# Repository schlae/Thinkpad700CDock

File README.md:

# Thinkpad 700C Dock Slot Adapter
This set of boards allows you to connect Micro Channel expansion boards to an IBM Thinkpad 700, 700C, 720, or 720C. This is an experimental project based on a lot of my own reverse engineering work, so don't expect it to work perfectly.

The AMP Champ connector appears to be out of production, so this project uses two stacked circuit boards that are slightly thinner (1.2mm) than a normal PC board. The 1.2mm thickness allows the boards, after stacking, to plug right into the docking connector.

## Fabbing and Assembly

Be sure to specify 1.2mm thickness for all the boards!

There are three boards total. The first two are both boards that plug into the lower part of the docking connector. Pick one of them.

* 700CDockSlot - Oriented so a connected Micro Channel card bracket points toward the left edge of the LCD display as viewed from the front. This provides easy access to the component side of the Micro Channel card from behind the laptop.
* 700CDockSlotFlipped - Oriented so a connected Micro Channel expansion card bracket sits at the right edge of the LCD display as viewed from the front. Turning the laptop around, you will see the solder side of an attached Micro Channel expansion card.

The third board plugs into the upper part of the docking connector.

* 700CDockSlotUpper - Provides wiring for IRQ10, IRQ11, IRQ12, IRQ14, and IRQ15.

If you know you won't need those IRQ lines, then you don't need this board.

Once you've soldered up both boards, attach them together using wires connecting the two boards together through J2. Use 1.6mm thick washers or 3D printed spacers in between the boards.

## Configuration

Jumper block J8 lets you select the source of the main 5V rail. Typically you will want to use the 5V position, which is an always-on 5V source. The 5VD position uses the 5V source that shuts off when the laptop is in standby mode. This isn't desirable since the laptop BIOS does not reinitialize and reenable any cards plugged into the adapter.

Test points J9 and J10 are for providing an external source of +12V for cards that require a lot of current (like hard cards or whatever).

## Known Issues

Revision 1 of the design had a few design errors that were fixed in rev 2. In case you have an old revision board, you will need to make the following changes:

* CHRESET should be tied to pin 102 of the docking connector. 
* MADE24 has not been found on the docking connector yet. Most likely this is because the machine never has more than 16M of RAM and it does not support 32-bit cards.

To fix the CHRESET issue, remove U3 and R3. Cut the MADE24 trace at the Micro Channel slot connector (pin A2) and run a wire from pin 102 of the expansion edge connector to U3 pin 2. Connect a 10K resistor from the MADE24 pin of the MCA bus connector (pin A2) to a nearby +5C net (like pin A7).

Signal integrity isn't all that good, but these older 5V logic systems were not known for good signal integrity. The original IBM docking cartridge uses some buffer chips presumably for improving this on some signals, but I don't have access to one nor do I have access to high-resolution photos, so the mystery remains.

Certain types of cards will not work with this setup. Memory cards that use the matched memory extension won't physically fit, and wouldn't work anyway because the 700C doesn't bring out the necessary bus signals. I have not wired up the signals for the Auxiliary Video Extension, so cards supporting this won't work either.

The docking connector brings out a single CD\_SETUP# signal for slot 2, limiting this adapter to a single card slot. In theory it would be possible to support more than one slot; more research is necessary.

# Thinkpad 700C Docking Connector Information
Through a rather tedious manual process, I've been able to reverse engineer the docking connector for this laptop.

| Bottom row (wide end) | Row 2 | Row 3 | Top row (narrow end) |
|-----------------------|-------|-------|----------------------|
| 1: PWR\_SWITCH#         | 61: CD\_SETUP# (slot 2) | 121: +5V              | 181: +5V |
| 2: Unknown, to 39G8600  | 62: GND                 | 122: +10V             | 182: +5V |
| 3: GND                  | 63: AUDIO SUM           | 123: GND              | 183: +5V |
| 4: OSC (14.318MHz)      | 64: GND                 | 124: PS/2 mouse pin 2 | 184: PS/2 mouse pin 1 | 
| 5: GND                  | 65: A23                 | 125: PS/2 mouse pin 6 | 185: PS/2 mouse pin 5 |
| 6: A6                   | 66: A22                 | 126: GND              | 186: GND |
| 7: +5V                  | 67: A21                 | 127: n/c              | 187: GND |
| 8: A5                   | 68: A20                 | 128: n/c              | 188: GND |
| 9: +5V                  | 69: A19                 | 129: n/c              | 189: GND |
| 10: A4                  | 70: A18                 | 130: n/c              | 190: n/c |
| 11: GND                 | 71: A17                 | 131: n/c              | 191: GND |
| 12: A3                  | 72: A16                 | 132: n/c              | 192: GND |
| 13: 5V\_2               | 73: A15                 | 133: n/c              | 193: GND |
| 14: A2                  | 74: A14                 | 134: n/c              | 194: n/c |
| 15: 5V\_2               | 75: A13                 | 135: n/c              | 195: GND |
| 16: A1                  | 76: A12                 | 136: n/c              | 196: GND |
| 17: 5V\_2               | 77: A11                 | 137: n/c              | 197: n/c |
| 18: A0                  | 78: A10                 | 138: n/c              | 198: n/c |
| 19: GND                 | 79: A9                  | 139: n/c              | 199: GND |
| 20: ADL#                | 80: A8                  | 140: n/c              | 200: n/c |
| 21: GND                 | 81: A7                  | 141: n/c              | 201: GND |
| 22: S0 (WR#)            | 82: PREEMPT#            | 142: n/c              | 202: n/c |
| 23: 5V\_2               | 83: BURST#              | 143: n/c              | 203: GND |
| 24: S1 (RD#)            | 84: IRQ9#               | 144: n/c              | 204: n/c |
| 25: 5V\_2               | 85: IRQ3#               | 145: LED5 (floppy)    | 205: LED1 (speaker green) |
| 26: M/IO#               | 86: IRQ4#               | 146: LED6 (HDD)       | 206: LED4 (left arrow) |
| 27: GND                 | 87: IRQ5#               | 147: REFRESH (positive) | 207: GND |
| 28: CMD#                | 88: IRQ6#               | 148: ESYNC# (AVE)     | 208: VSYNC (AVE) |
| 29: GND                 | 89: IRQ7#               | 149: P7 (AVE)         | 209: HSYNC (AVE) |
| 30: ARB/GNT#            | 90: ARB0                | 150: P6 (AVE)         | 210: BLANK (AVE) |
| 31: n/c                 | 91: ARB1                | 151: P5 (AVE)         | 211: GND |
| 32: TC#                 | 92: ARB2                | 152: P4 (AVE)         | 212: DCLK (AVE) |
| 33: GND                 | 93: ARB3                | 153: P3 (AVE)         | 213: GND |
| 34: CHRDY#              | 94: CHCK#               | 154: P2 (AVE)         | 214: GND |
| 35: n/c                 | 95: CHRDYRTN#           | 155: P1 (AVE)         | 215: EDCLK# |
| 36: CD\_SFDBK#          | 96: DB0                 | 156: P0 (AVE)         | 216: EVIDEO# |
| 37: GND                 | 97: DB1                 | 157: Unknown, goes to 39G8600 | 217: GND |
| 38: DB3                 | 98: DB2                 | 158: IRQ11#           | 218: IRQ10# |
| 39: n/c                 | 99: DB4                 | 159: IRQ14#           | 219: IRQ12# |
| 40: DB6                 | 100: DB5                | 160: n/c (pulled up)  | 220: IRQ15# |
| 41: GND                 | 101: DB7                | 161: n/c (pulled up)  | 221: n/c (pulled up) |
| 42: CD\_DS16RTN#        | 102: CHRESET            | 162: n/c              | 222: GND |
| 43: n/c                 | 103: REFRESH#           | 163: Parallel port pin 9 | 223: Parallel port pin 13 |
| 44: +5V                 | 104: DB8                | 164: Parallel port pin 8 | 224: Parallel port pin 12 |
| 45: +5V                 | 105: DB9                | 165: Parallel port pin 7 | 225: Parallel port pin 11 |
| 46: DB11                | 106: DB10               | 166: Parallel port pin 6 | 226: GND |
| 47: GND                 | 107: DB12               | 167: Parallel port pin 5 | 227: Parallel port pin 10 |
| 48: GND                 | 108: DB13               | 168: Parallel port pin 4 | 228: Parallel port pin 17 |
| 49: n/c                 | 109: DB14               | 169: Parallel port pin 3 | 229: Parallel port pin 16 |
| 50: GND                 | 110: DB15               | 170: Parallel port pin 2 | 230: Parallel port pin 15 |
| 51: n/c                 | 111: CD\_DS16#          | 171: Parallel port pin 1 | 231: Parallel port pin 14 |
| 52: n/c                 | 112: SBHE#              | 172: STANDBY# (CN4 64) | 232: GND |
| 53: GND                 | 113: GND                | 173: Serial port pin 3   | 233: Serial port pin 2 |
| 54: +20V AC adapter     | 114: VGA port pin 3     | 174: Serial port pin 1   | 233: Serial port pin 4 |
| 55: +20V AC adapter     | 115: GND                | 175: Serial port pin 6   | 234: Serial port pin 8 |
| 56: +20V AC adapter     | 116: VGA port pin 2     | 176: Serial port pin 7   | 235: Serial port pin 9 |
| 57: +20V AC adapter     | 117: GND                | 177: VGA port pin 4      | 237: VGA port pin 15 |
| 58: +20V AC adapter     | 118: VGA port pin 1     | 178: VGA port pin 11     | 238: VGA port pin 12 |
| 59: +20V AC adapter     | 119: GND                | 179: +10V                | 239: GND |
| 60: +20V AC adapter     | 120: BACKLIGHT\_PWR# (CN4 29) | 180: GND | 240: GND |

Notes:

* 5V\_2 pins are always on. All remaining +5V pins turn off in standby mode.
* STANDBY# is at ~13V when the laptop is off, 5V during normal operation, and 0V during standby.

**Pin diagram (looking into the back of the laptop)**

The docking connector is in the AMP Champ .050 family, similar to the 5787886-1 but with 240 contacts instead of 200. I've had success connecting to the docking port using two stacked PCBs with 0.050" edge fingers. The PCBs need to be 1.2mm thick instead of the normal 1.6mm.

The docking port breaks out several ports on the laptop, for convenience:
* Parallel port
* Serial port
* PS/2 mouse port
* VGA port
* AC adapter

There also also all the signals required to implement a single Micro Channel expansion slot, including the Auxiliary Video Extension (AVE). This does not include the +12V and -12V rails. It also does not appear to break out the CHRESET signal.

Several pins implement functions specific to this laptop, including:
* PWR\_SWITCH#: Bring this line low to turn on the laptop. Connected in parallel with the physical power switch.
* LED1, LED4, LED5, LED6: Presumably a docking station could duplicate these LEDs (or perhaps control them?)
* SOFT\_POWEROFF#: Tied to the power board's connector pin 64.
* BACKLIGHT\_PWR#: Tied to the power board's connector pin 29.

# Thinkpad 700C Hard Disk Connector

The pinout for the hard disk drive is as follows:

| Pin | Function | Pin | Function |
|-----|----------|-----|----------|
| 1 | CHRESET#?  | 2 | CHRESET |
| 3 | SBHE#      | 4 | +5V |
| 5 | (key)      | 6 | S0 (WR#) |
| 7 | GND        | 8 | S1 (RD#) |
| 9 | CHRDY#     | 10 | GND |
| 11 | CMD# (buffered) | 12 | A3 |
| 13 | A2        | 14 | A1 |
| 15 | M/IO#     | 16 | A0 |
| 17 | ARB/GNT#  | 18 | TC# |
| 19 | IRQ14#    | 20 | DB13 |
| 21 | GND       | 22 | DB11 |
| 23 | DB10      | 24 | DB7 |
| 25 | ARB3      | 26 | ARB2 |
| 27 | GND       | 28 | ARB1 |
| 29 | ARB0      | 30 | BURST# |
| 31 | PREEMPT#  | 32 | DB6 |
| 33 | GND       | 34 | DB5 |
| 35 | DB2       | 36 | +5V |
| 37 | DB0       | 38 | DB15 |
| 39 | GND       | 40 | DB14 |
| 41 | DB12      | 42 | DB9 |
| 43 | GND       | 44 | DB8 |
| 45 | DB4       | 46 | +5V |
| 47 | DB3       | 48 | DB1 |
| 49 | GND       | 50 | CD\_DS16# (buffered) |
| 51 | CD\_SETUP# (slot 1) | 52 | ADDRESS\_SEL# |
| 53 | n/c | 54 | n/c |
| 55 | n/c | 56 | n/c |
| 57 | n/c | 58 | n/c |
| 59 | n/c | 60 | n/c |

Note: CHRESET# is inverted from the usual MCA CHRESET signal. It goes low to reset the drive.

The hard drive connector goes through a flex connection to a 52-pin 2mm header on the actual hard drive itself. The pinout matches 1:1. Pins 53-60 are not wired through. The motherboard connector is probably from the AMP Champ .050 FH family: 5176381-2. Possible matching connectors include the AMP 5176376-2 and the 5176379-2.

The hard drive is of the DBA (direct bus attach) ESDI type, and shows up as slot 1. (Slot 2 is on the docking connector.)

The ADDRESS\_SEL# output goes low when the address range assigned to the hard drive shows up on the address bus: 0x351x). It does not go low during card setup mode (CD\_SETUP# pulled low), which seems to only use the 4 address bits to decode the POS registers.

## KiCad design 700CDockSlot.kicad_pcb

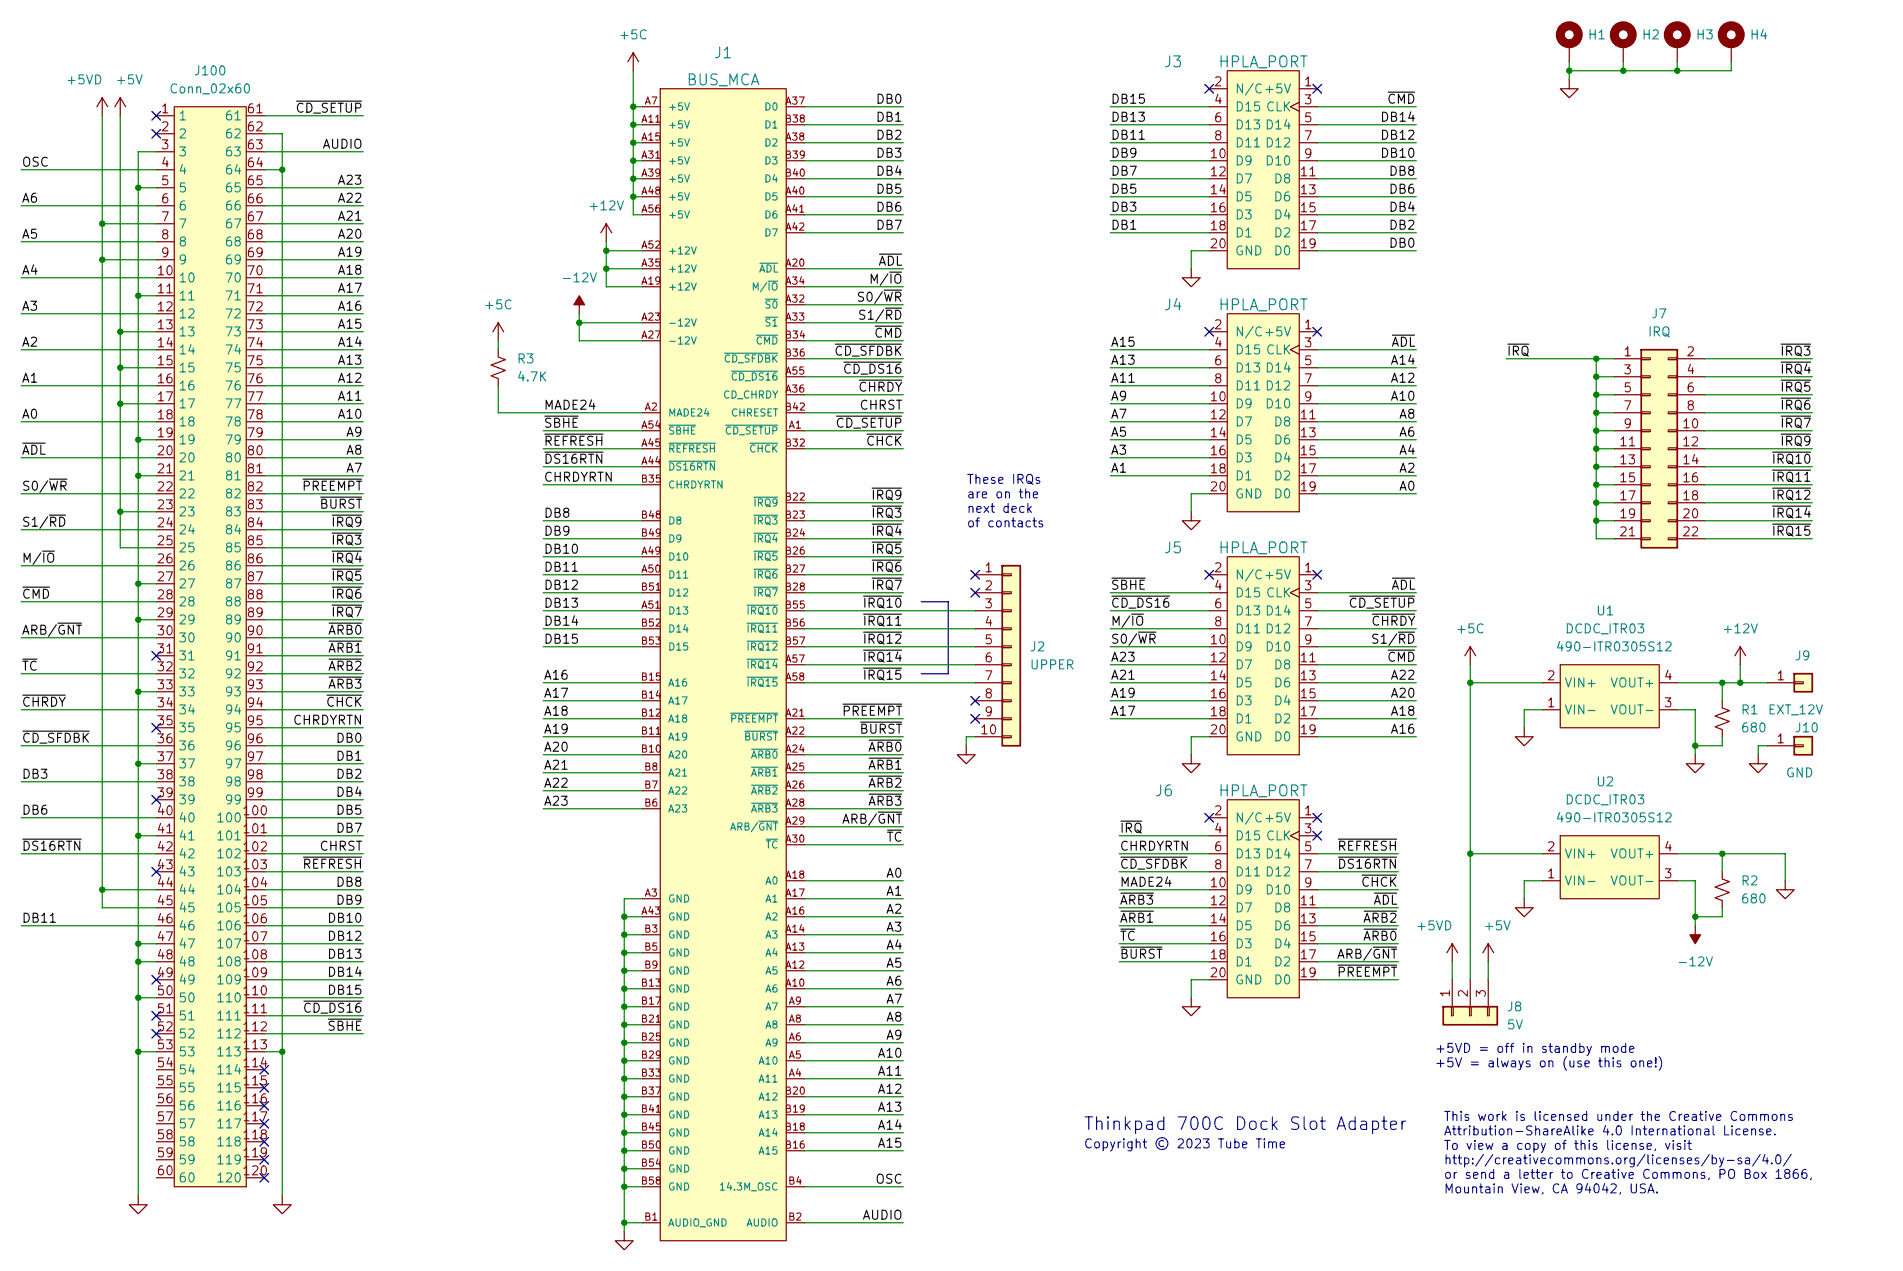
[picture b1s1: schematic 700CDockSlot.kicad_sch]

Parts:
H1, H2, H3, H4: MountingHole_Pad; MountingHole_3.2mm_M3_DIN965_Pad
J1: BUS_MCA; SLOT_MCA_16BIT; Mouser 571-5650090-1
J2: UPPER; PinHeader_1x10_P2.54mm_Vertical
J3, J4, J5, J6: HPLA_PORT; PinHeader_2x10_P2.54mm_Vertical
J7: IRQ; PinHeader_2x11_P2.54mm_Vertical
J8: 5V; PinHeader_1x03_P2.54mm_Vertical
J9: EXT_12V; TestPoint_Keystone_5005-5009_Compact
J10: GND; TestPoint_Keystone_5005-5009_Compact
J100: Conn_02x60; DockFootprint
R1, R2: 680; RESC2012X55
R3: 4.7K; RESC1608X55
U1, U2: DCDC_ITR03; Mouser 490-ITR0305S12

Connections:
+5C: J1.A7 (+5V), J1.A11 (+5V), J1.A15 (+5V), J1.A31 (+5V), J1.A39 (+5V), J1.A48 (+5V), J1.A56 (+5V), J8.2, R3.1, U1.2 (VIN+), U2.2 (VIN+)
+5V: J8.3, J100.13, J100.15, J100.17, J100.23, J100.25
+5VD: J8.1, J100.7, J100.9, J100.44, J100.45
+12V: J1.A19 (+12V), J1.A35 (+12V), J1.A52 (+12V), J9.1, R1.1, U1.4 (VOUT+)
-12V: J1.A23 (-12V), J1.A27 (-12V), R2.2, U2.3 (VOUT-)
/A0: J1.A18 (A0), J4.19 (D0), J100.18
/A1: J1.A17 (A1), J4.18 (D1), J100.16
/A2: J1.A16 (A2), J4.17 (D2), J100.14
/A3: J1.A14 (A3), J4.16 (D3), J100.12
/A4: J1.A13 (A4), J4.15 (D4), J100.10
/A5: J1.A12 (A5), J4.14 (D5), J100.8
/A6: J1.A10 (A6), J4.13 (D6), J100.6
/A7: J1.A9 (A7), J4.12 (D7), J100.81
/A8: J1.A8, J4.11 (D8), J100.80
/A9: J1.A6 (A9), J4.10 (D9), J100.79
/A10: J1.A5 (A10), J4.9 (D10), J100.78
/A11: J1.A4 (A11), J4.8 (D11), J100.77
/A12: J1.B20 (A12), J4.7 (D12), J100.76
/A13: J1.B19 (A13), J4.6 (D13), J100.75
/A14: J1.B18 (A14), J4.5 (D14), J100.74
/A15: J1.B16 (A15), J4.4 (D15), J100.73
/A16: J1.B15 (A16), J5.19 (D0), J100.72
/A17: J1.B14 (A17), J5.18 (D1), J100.71
/A18: J1.B12 (A18), J5.17 (D2), J100.70
/A19: J1.B11 (A19), J5.16 (D3), J100.69
/A20: J1.B10 (A20), J5.15 (D4), J100.68
/A21: J1.B8 (A21), J5.14 (D5), J100.67
/A22: J1.B7 (A22), J5.13 (D6), J100.66
/A23: J1.B6 (A23), J5.12 (D7), J100.65
/ARB/~GNT: J1.A29 (ARB/~GNT), J6.17 (D2), J100.30
/AUDIO: J1.B2 (AUDIO), J100.63
/CHRDYRTN: J1.B35 (CHRDYRTN), J6.6 (D13), J100.95
/CHRST: J1.B42 (CHRESET), J100.102
/DB0: J1.A37 (D0), J3.19 (D0), J100.96
/DB1: J1.B38 (D1), J3.18 (D1), J100.97
/DB2: J1.A38 (D2), J3.17 (D2), J100.98
/DB3: J1.B39 (D3), J3.16 (D3), J100.38
/DB4: J1.B40 (D4), J3.15 (D4), J100.99
/DB5: J1.A40 (D5), J3.14 (D5), J100.100
/DB6: J1.A41 (D6), J3.13 (D6), J100.40
/DB7: J1.A42 (D7), J3.12 (D7), J100.101
/DB8: J1.B48 (D8), J3.11 (D8), J100.104
/DB9: J1.B49 (D9), J3.10 (D9), J100.105
/DB10: J1.A49 (D10), J3.9 (D10), J100.106
/DB11: J1.A50 (D11), J3.8 (D11), J100.46
/DB12: J1.B51 (D12), J3.7 (D12), J100.107
/DB13: J1.A51 (D13), J3.6 (D13), J100.108
/DB14: J1.B52 (D14), J3.5 (D14), J100.109
/DB15: J1.B53 (D15), J3.4 (D15), J100.110
/MADE24: J1.A2 (MADE24), J6.10 (D9), R3.2
/M/~IO: J1.A34 (M/~IO), J5.8 (D11), J100.26
/OSC: J1.B4 (14.3M_OSC), J100.4
/S0/~WR: J1.A32 (~S0), J5.10 (D9), J100.22
/S1/~RD: J1.A33 (~S1), J5.9 (D10), J100.24
/~ADL: J1.A20 (~ADL), J4.3 (CLK), J5.3 (CLK), J6.11 (D8), J100.20
/~ARB0: J1.A24 (~ARB0), J6.15 (D4), J100.90
/~ARB1: J1.A25 (~ARB1), J6.14 (D5), J100.91
/~ARB2: J1.A26 (~ARB2), J6.13 (D6), J100.92
/~ARB3: J1.A28 (~ARB3), J6.12 (D7), J100.93
/~BURST: J1.A22 (~BURST), J6.18 (D1), J100.83
/~CD_DS16: J1.A55 (~CD_DS16), J5.6 (D13), J100.111
/~CD_SETUP: J1.A1 (~CD_SETUP), J5.5 (D14), J100.61
/~CD_SFDBK: J1.B36 (~CD_SFDBK), J6.8 (D11), J100.36
/~CHCK: J1.B32 (~CHCK), J6.9 (D10), J100.94
/~CHRDY: J1.A36 (CD_CHRDY), J5.7 (D12), J100.34
/~CMD: J1.B34 (~CMD), J3.3 (CLK), J5.11 (D8), J100.28
/~DS16RTN: J1.A44 (~DS16RTN), J6.7 (D12), J100.42
/~IRQ3: J1.B23 (~IRQ3), J7.2, J100.85
/~IRQ4: J1.B24 (~IRQ4), J7.4, J100.86
/~IRQ5: J1.B26 (~IRQ5), J7.6, J100.87
/~IRQ6: J1.B27 (~IRQ6), J7.8, J100.88
/~IRQ7: J1.B28 (~IRQ7), J7.10, J100.89
/~IRQ9: J1.B22 (~IRQ9), J7.12, J100.84
/~IRQ10: J1.B55 (~IRQ10), J2.3, J7.14
/~IRQ11: J1.B56 (~IRQ11), J2.4, J7.16
/~IRQ12: J1.B57 (~IRQ12), J2.5, J7.18
/~IRQ14: J1.A57 (~IRQ14), J2.6, J7.20
/~IRQ15: J1.A58 (~IRQ15), J2.7, J7.22
/~IRQ: J6.4 (D15), J7.1, J7.3, J7.5, J7.7, J7.9, J7.11, J7.13, J7.15, J7.17, J7.19, J7.21
/~PREEMPT: J1.A21 (~PREEMPT), J6.19 (D0), J100.82
/~REFRESH: J1.A45 (~REFRESH), J6.5 (D14), J100.103
/~SBHE: J1.A54 (~SBHE), J5.4 (D15), J100.112
/~TC: J1.A30 (~TC), J6.16 (D3), J100.32
GND: H1.1, H2.1, H3.1, H4.1, J1.A3 (GND), J1.A43 (GND), J1.B1 (AUDIO_GND), J1.B3 (GND), J1.B5 (GND), J1.B9 (GND), J1.B13 (GND), J1.B17 (GND), J1.B21 (GND), J1.B25 (GND), J1.B29 (GND), J1.B33 (GND), J1.B37 (GND), J1.B41 (GND), J1.B45 (GND), J1.B50 (GND), J1.B54 (GND), J1.B58 (GND), J2.10, J3.20 (GND), J4.20 (GND), J5.20 (GND), J6.20 (GND), J10.1, J100.3, J100.5, J100.11, J100.19, J100.21, J100.27, J100.29, J100.33, J100.37, J100.41, J100.47, J100.48, J100.50, J100.53, J100.62, J100.64, J100.113, R1.2, R2.1, U1.1 (VIN-), U1.3 (VOUT-), U2.1 (VIN-), U2.4 (VOUT+)

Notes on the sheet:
These IRQs are on the next deck of contacts
This work is licensed under the Creative Commons Attribution-ShareAlike 4.0 International License. To view a copy of this license, visit http://creativecommons.org/licenses/by-sa/4.0/ or send a letter to Creative Commons, PO Box 1866, Mountain View, CA 94042, USA.
Copyright © 2023 Tube Time
Thinkpad 700C Dock Slot Adapter
+5VD = off in standby mode +5V = always on (use this one!)

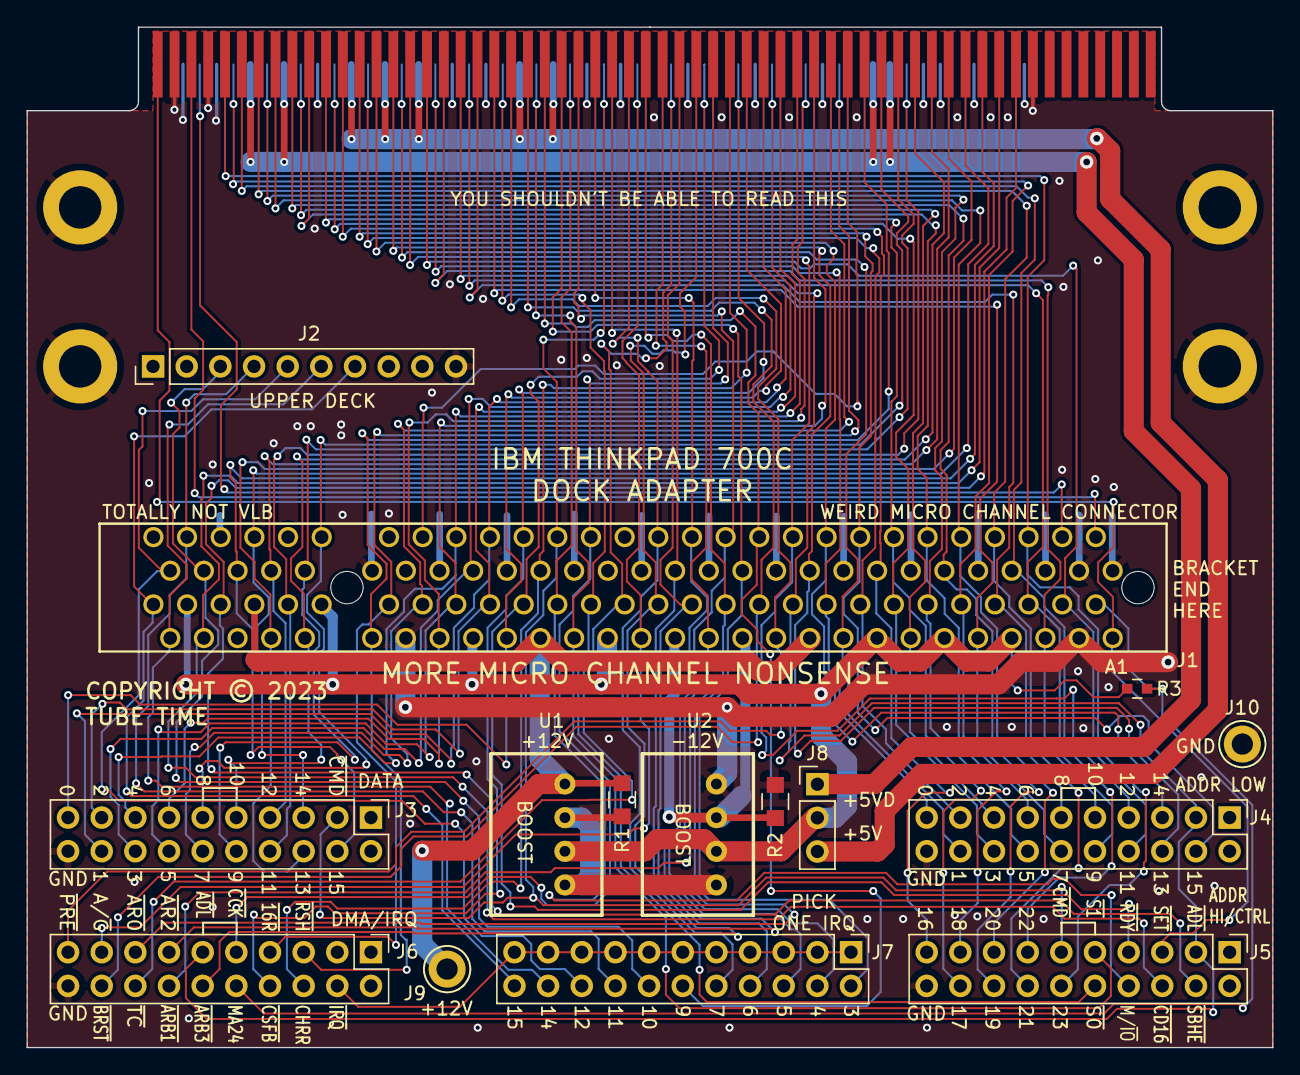
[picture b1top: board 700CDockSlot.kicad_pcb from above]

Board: 2 copper layers, 94.0 x 77.0 mm, 20 parts (0 on the bottom side), 84 nets.

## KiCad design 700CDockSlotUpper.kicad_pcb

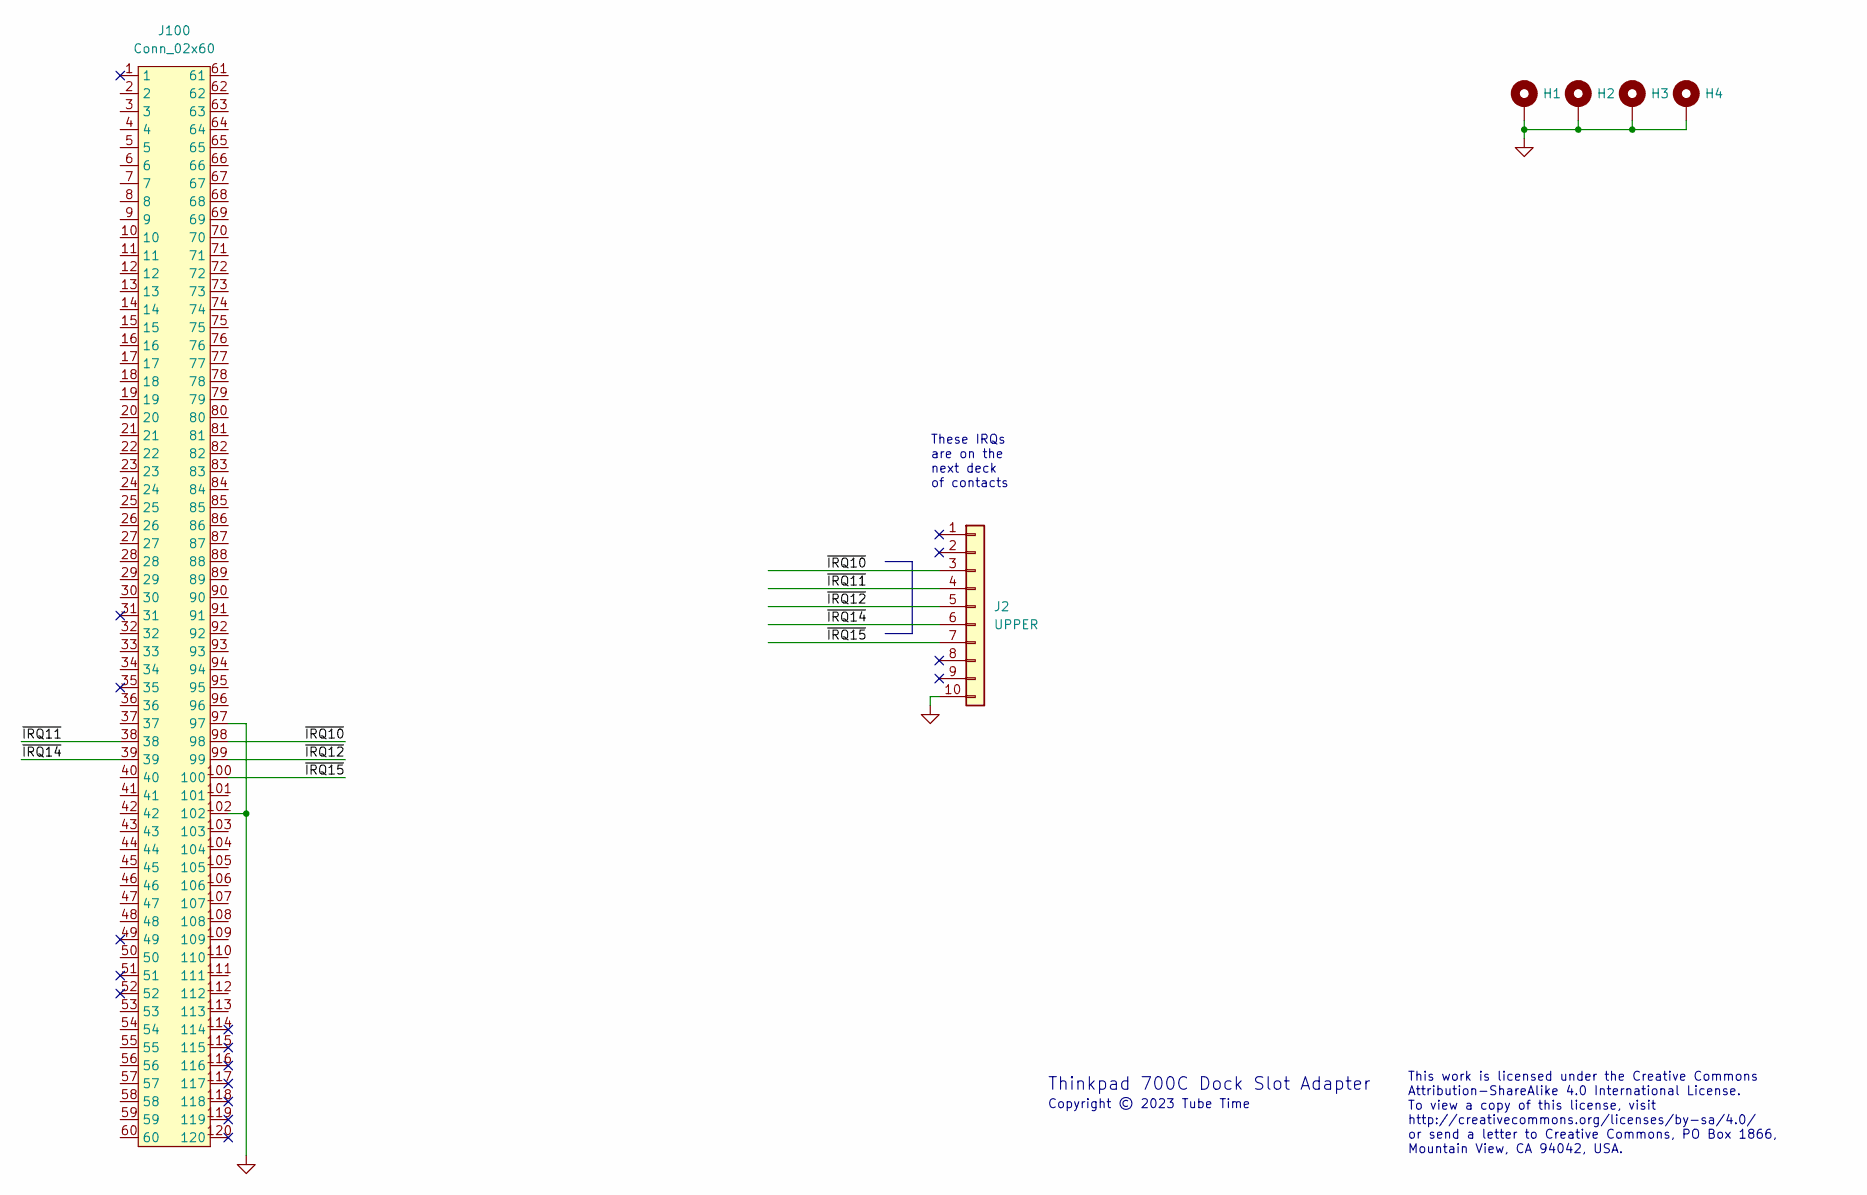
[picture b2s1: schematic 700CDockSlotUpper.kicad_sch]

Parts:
H1, H2, H3, H4: MountingHole_Pad; MountingHole_3.2mm_M3_DIN965_Pad
J2: UPPER; PinHeader_1x10_P2.54mm_Vertical
J100: Conn_02x60; DockFootprint

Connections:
/~IRQ10: J2.3, J100.98
/~IRQ11: J2.4, J100.38
/~IRQ12: J2.5, J100.99
/~IRQ14: J2.6, J100.39
/~IRQ15: J2.7, J100.100
GND: H1.1, H2.1, H3.1, H4.1, J2.10, J100.97, J100.102

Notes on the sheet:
These IRQs are on the next deck of contacts
This work is licensed under the Creative Commons Attribution-ShareAlike 4.0 International License. To view a copy of this license, visit http://creativecommons.org/licenses/by-sa/4.0/ or send a letter to Creative Commons, PO Box 1866, Mountain View, CA 94042, USA.
Copyright © 2023 Tube Time
Thinkpad 700C Dock Slot Adapter

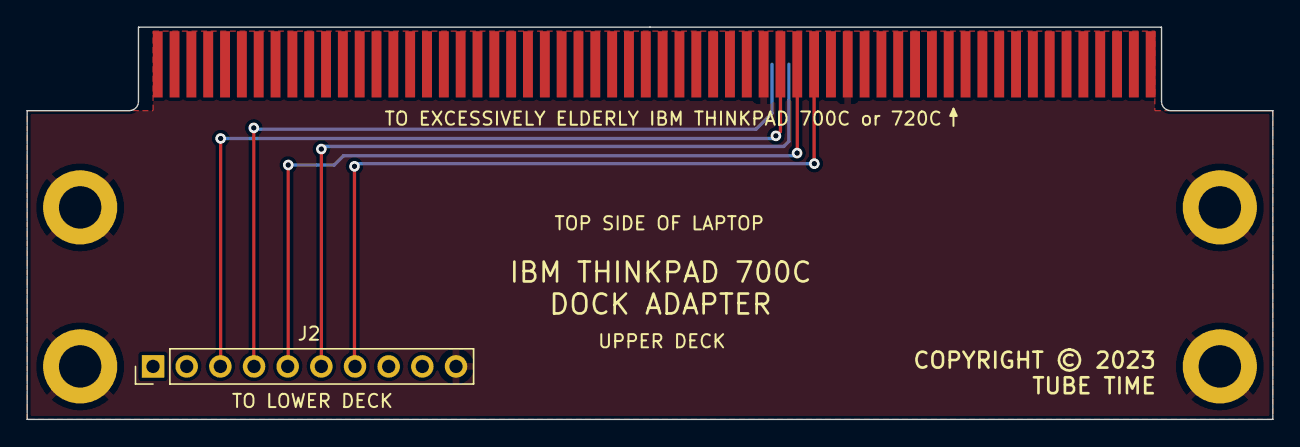
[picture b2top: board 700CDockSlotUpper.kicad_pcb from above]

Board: 2 copper layers, 94.0 x 29.6 mm, 6 parts (0 on the bottom side), 6 nets.

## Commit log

2023-07-04 Add pinout diagram
2023-08-18 MADE24 is actually CHRESET.
2023-08-18 Add detail on the missing MADE24 signal
2023-10-07 Card setup and address selected clarification
2024-06-03 Rev 2: Fix CHRESET, disconnect and pull up MADE24

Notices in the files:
700CDockSlot.kicad_pcb:
Copyright (C) 2023 Tube Time
